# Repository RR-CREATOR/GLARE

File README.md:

# GLARE  
**Glasses Linked Augmented Reality Engine // By RR-CREATOR (rrop)**

---

## Table of Contents
- [GLARE](#glare)
  - [Intro](#intro)
  - [Why I made this](#why-i-made-this)
  - [PCB](#pcb)
    - [Power](#power)
    - [Main](#main)
    - [Full Board](#full-board)
  - [CAD](#cad)
    - [HUD](#hud)
    - [Camera](#camera)
    - [Frame](#frame)
    - [FULL CAD](#full-cad)
  - [BOM](#bom)

---

## GLARE

### Intro
GLARE is a Glasses Linked Augmented Reality Engine.  
It is basically a glasses attachment.  
It has a custom pcb, which you could place either inside the frame of glasses if you 3d print the frame, or attach it outside.  
It has a custom HUD made using birdbath optics and a 0.39" display, on one side, so you aren't too disconnected with reality, and a lot of the issues caused by cheap optics are resolved through seperate vision.  
It features an esp32-s3-wroom-n16r8 motherboard which, along with a phone(to be added after testing pcb), will get data from 2 mics, a camera, a gyro and gps and give an Augmented Reality experience through the HUD, for assitance in day to day life.

### Why I made this
I made this as I wanted to build something cheap and accessible, which could make AR glasses a reality for people.
I wanted it to be able to help people in need by translating written text it sees into users chosen language, and it can also
listen to conversations and show a live transcript in users chosen language, and can work for sign language as well.

---

## PCB
It has a custom pcb which serves as its mainboard.

### Power
The pcb has proper power management, and is powered by two batteries in parallel connected to a voltage supervisor.

The pcb also has a micro usb b port which is used to charge the LiPo batteries and is also used for programming the esp 32 module on the board.

It also has a battery gauge, and a power on/off button, along with a low power isolation.

It also has a 5V boost and a 5V to 3.3V LDO to power esp and other peripherals.

### Main
The pcb also has connections for various peripherals, including 2 mics for stereo sound, a camera, a micro oled display, a gps and gyro.

It also has a usb to uart module to programme this esp 32.

### Full Board

**Fully Traced Board:**  

**3D Model of PCB:**  

> Ik the pcb looks lik a cheap cybertruck :3

---

## CAD

### HUD
So the CAD has a representation of the HUD, attached to a small piece, to attach it to the frame.  
(the pieces of the hud will be glued with optically clear glue)

### Camera
It also has a small holder where the camera will go. The holder has an extended piece using which it will be glued to the glasses.

### Frame
The right leg/handle of the glasses frame has a simple design, with its bottom looking like a battery.

The left leg/handle on the other hand is modelled around the shape of the pcb, and is hollow with a cover so that the pcb can be enclosed in it.  
Also, it bottom is hollow, and designed so that a battery can be placed inside it.

### FULL CAD

---

## BOM

<table>
    <tr>
        <td>Category</td>
        <td>Component</td>
        <td>Part Number / Source</td>
        <td>Price (USD)</td>
        <td>Quantity</td>
        <td>Notes</td>
    </tr>
    <tr>
        <td>Core</td>
        <td>ESP32-S3-WROOM-1U-N16R8</td>
        <td>https://lcsc.com/product-detail/WiFi-Modules_ESPRESSIF-ESP32-S3-WROOM-1U-N16R8_C3013946.html?s_z=n_ESP32-S3-WROOM-1U-N16R8</td>
        <td>5.66</td>
        <td>1</td>
        <td>Core chip with wifi and bt</td>
    </tr>
    <tr>
        <td>Antenna</td>
        <td>Ezurio 001-0014</td>
        <td>https://www.digikey.com/en/products/detail/ezurio/001-0014/4732758</td>
        <td>3.41</td>
        <td>1</td>
        <td>2.4GHz for core</td>
    </tr>
    <tr>
        <td>Mosfet</td>
        <td>PMZ350UPEYL</td>
        <td>https://lcsc.com/product-detail/MOSFETs_Nexperia-PMZ350UPEYL_C478207.html?s_z=n_PMZ350UPEYL</td>
        <td>0.43</td>
        <td>10</td>
        <td>For display power switch</td>
    </tr>
    <tr>
        <td>USB to UART</td>
        <td>CH9102F</td>
        <td>https://lcsc.com/product-detail/USB-Converters_WCH-CH9102F_C2858418.html?s_z=n_CH9102F</td>
        <td>1.33</td>
        <td>1</td>
        <td>For Programming</td>
    </tr>
    <tr>
        <td>I�S Microphone</td>
        <td>SPH0645LM4H-B-8</td>
        <td>https://lcsc.com/product-detail/MEMS-Microphones_Knowles-SPH0645LM4H-B-8_C19190864.html?s_z=n_SPH0645LM4H-B</td>
        <td>8</td>
        <td>2</td>
        <td>MEMS microphone</td>
    </tr>
    <tr>
        <td>Transistors</td>
        <td>2SC4617R</td>
        <td>https://lcsc.com/product-detail/Bipolar-BJT_CBI-2SC4617R_C2836080.html?s_z=n_2SC4617R%2520BR</td>
        <td>0.35</td>
        <td>20</td>
        <td>Programming</td>
    </tr>
    <tr>
        <td>RGB LEDs</td>
        <td>WS2812B 2020</td>
        <td>https://lcsc.com/product-detail/RGB-LEDs-Built-in-IC_Worldsemi-WS2812B-2020_C965555.html?s_z=n_ws2812b%25202020</td>
        <td>0.41</td>
        <td>5</td>
        <td>For visual indication</td>
    </tr>
    <tr>
        <td>Micro USB B</td>
        <td>1050170001</td>
        <td>https://lcsc.com/product-detail/USB-Connectors_MOLEX-1050170001_C136000.html?s_z=n_C136000</td>
        <td>1.67</td>
        <td>1</td>
        <td>Charging LiPo</td>
    </tr>
    <tr>
        <td>Battery Charger</td>
        <td>AP5054HTCER</td>
        <td>https://lcsc.com/product-detail/Battery-Management_Wuxi-Chipown-Micro-electronics-AP5054HTCER_C2843820.html?s_z=n_ap5054htc</td>
        <td>0.15</td>
        <td>1</td>
        <td>Charging LiPo</td>
    </tr>
    <tr>
        <td>Low Voltage Detector</td>
        <td>XC61CC3002MR-G</td>
        <td>https://lcsc.com/product-detail/Supervisor-and-Reset-ICs_TOREX-XC61CC3002MR-G_C2456347.html?s_z=n_XC61CC3002MR</td>
        <td>0.92</td>
        <td>5</td>
        <td>Voltage Supervisor</td>
    </tr>
    <tr>
        <td>Battery Fuel Gauge</td>
        <td>MAX17048</td>
        <td>https://lcsc.com/product-detail/Battery-Management-ICs_Maxim-Integrated-MAX17048G-T10_C2682616.html</td>
        <td>4.16</td>
        <td>1</td>
        <td>Battery Percent</td>
    </tr>
    <tr>
        <td>Voltage Boost</td>
        <td>SY7088</td>
        <td>https://lcsc.com/product-detail/DC-DC-Converters_Silergy-SY7088DGC_C178240.html?s_z=n_SY7088</td>
        <td>1.52</td>
        <td>5</td>
        <td>Convert input to 5V</td>
    </tr>
    <tr>
        <td>LDO</td>
        <td>NCP167BMX330TBG</td>
        <td>https://lcsc.com/product-detail/Voltage-Regulators-Linear-Low-Drop-Out-LDO-Regulators_onsemi-NCP167BMX330TBG_C892227.html?s_z=n_NCP167BMX330TBG</td>
        <td>0.44</td>
        <td>1</td>
        <td>Convert 5V to 3.3V</td>
    </tr>
    <tr>
        <td>Schottky Diode</td>
        <td>RB160M-30</td>
        <td>https://lcsc.com/product-detail/Schottky-Diodes_High-Diode-RB160M-30_C2937163.html?s_z=n_C2937163</td>
        <td>0.38</td>
        <td>5</td>
        <td>Prevent back current in battery bypass</td>
    </tr>
    <tr>
        <td>Camera Module</td>
        <td>0V5640 160 AF</td>
        <td>https://www.aliexpress.com/item/3256806547258124.html?spm=a2g0o.productlist.main.7.3c04XpCAXpCAlF&amp;algo_pvid=1d8c60dc-197a-45e0-b911-5db3740a960b&amp;algo_exp_id=1d8c60dc-197a-45e0-b911-5db3740a960b-6&amp;pdp_ext_f=%7B%22order%22%3A%2248%22%2C%22eval%22%3A%221%22%7D&amp;pdp_npi=4%40dis%21USD%2125.14%216.32%21%21%21179.58%2145.16%21%40211b807017537824501694005e7310%2112000038123858641%21sea%21US%216130365553%21ABX&amp;curPageLogUid=NL6oj7jsGhIm&amp;utparam-url=scene%3Asearch%7Cquery_from%3A#nav-specification</td>
        <td>12.75</td>
        <td>1</td>
        <td>5MP autofocus camera</td>
    </tr>
    <tr>
        <td>Gyro + Accelo + Magneto</td>
        <td>ICM-20948</td>
        <td>https://lcsc.com/search?q=ICM-20948&amp;s_z=n_ICM-20948</td>
        <td>4.68</td>
        <td>1</td>
        <td>6-axis IMU</td>
    </tr>
    <tr>
        <td>GPS Module</td>
        <td>L86-M33</td>
        <td>https://www.mouser.in/ProductDetail/Quectel/L86-M33?qs=GedFDFLaBXFvEvNOo6IDYg%3D%3D</td>
        <td>12.82</td>
        <td>1</td>
        <td>Low-power GPS module</td>
    </tr>
    <tr>
        <td>Micro Oled Display</td>
        <td>ET039XGM OLED display + HDMI driver board</td>
        <td>Alibaba (including shipping) </td>
        <td>30</td>
        <td>1</td>
        <td>For HUD</td>
    </tr>
    <tr>
        <td>Mosfet main battery</td>
        <td>YJQD30P02A</td>
        <td>https://lcsc.com/product-detail/MOSFETs_YANGJIE-YJQD30P02A_C919546.html?s_z=n_C919546</td>
        <td>1.36</td>
        <td>5</td>
        <td>Mosfet for high power switching</td>
    </tr>
    <tr>
        <td>Mosfet main battery</td>
        <td>PMZ290UNE2YL</td>
        <td>https://lcsc.com/product-detail/MOSFETs_Nexperia-PMZ290UNE2YL_C478155.html?s_z=n_C478155</td>
        <td>0.53</td>
        <td>10</td>
        <td>Mosfet for high power switching</td>
    </tr>
    <tr>
        <td>Resistor</td>
        <td>10k ohm</td>
        <td>https://lcsc.com/product-detail/Chip-Resistor-Surface-Mount_FOJAN-FRC0402J103-TS_C2906885.html?s_z=n_C2906885</td>
        <td>0.05</td>
        <td>100</td>
        <td>Resistor</td>
    </tr>
    <tr>
        <td>Resistor</td>
        <td>150ohm</td>
        <td>https://lcsc.com/product-detail/Chip-Resistor-Surface-Mount_FOJAN-FRC0402F1500TS_C2909321.html?s_z=n_150ohm%2520resistor%25200402</td>
        <td>0.05</td>
        <td>100</td>
        <td>Resistor</td>
    </tr>
    <tr>
        <td>Resistor</td>
        <td>100k ohm</td>
        <td>https://lcsc.com/product-detail/Chip-Resistor-Surface-Mount_YAGEO-RC0402JR-07100KL_C106234.html?s_z=n_C106234</td>
        <td>0.06</td>
        <td>100</td>
        <td>Resistor</td>
    </tr>
    <tr>
        <td>Resistor</td>
        <td>2k ohm</td>
        <td>https://lcsc.com/product-detail/Chip-Resistor-Surface-Mount_YAGEO-RC0402FR-072KL_C60488.html?s_z=n_C60488</td>
        <td>0.06</td>
        <td>100</td>
        <td>Resistor</td>
    </tr>
    <tr>
        <td>Resistor</td>
        <td>1M ohm</td>
        <td>https://lcsc.com/product-detail/Chip-Resistor-Surface-Mount_YAGEO-RC0402FR-071ML_C138033.html</td>
        <td>0.07</td>
        <td>100</td>
        <td>Resistor</td>
    </tr>
    <tr>
        <td>Resistor</td>
        <td>470k</td>
        <td>https://lcsc.com/product-detail/Chip-Resistor-Surface-Mount_YAGEO-AC0402JR-07470KL_C227380.html</td>
        <td>0.05</td>
        <td>100</td>
        <td>Resistor</td>
    </tr>
    <tr>
        <td>Resistor/Resettable Fuse</td>
        <td>1A</td>
        <td>https://lcsc.com/product-detail/Resettable-Fuses_JDTfuse-ASMD0805-100_C135331.html?s_z=n_%2509%25206V%25201A%2520100A%25201.95A%25200805%2520Resettable%2520Fuses%2520ROHS</td>
        <td>0.44</td>
        <td>10</td>
        <td>Charging LiPo</td>
    </tr>
    <tr>
        <td>Resistor</td>
        <td>147k</td>
        <td>https://lcsc.com/product-detail/Chip-Resistor-Surface-Mount_YAGEO-AC0402FR-07147KL_C226785.html</td>
        <td>0.11</td>
        <td>100</td>
        <td>Resistor</td>
    </tr>
    <tr>
        <td>Switch</td>
        <td>SPST Tactile Switch</td>
        <td>https://lcsc.com/product-detail/Tactile-Switches_USAKRO-UK-B0249-SP25Y_C493280.html</td>
        <td>0.85</td>
        <td>5</td>
        <td>User button</td>
    </tr>
    <tr>
        <td>Switch</td>
        <td>Slide Switch</td>
        <td>https://lcsc.com/product-detail/Slide-Switches_Korean-Hroparts-Elec-K3-1270L-F1_C145858.html?s_z=n_C145858</td>
        <td>0.72</td>
        <td>5</td>
        <td>Power on/off</td>
    </tr>
    <tr>
        <td>LiPo battery</td>
        <td>500mAh, 3.7V</td>
        <td>https://robu.in/product/500mah-pcm-protected-micro-li-po-battery-2/</td>
        <td>6</td>
        <td>2</td>
        <td>For power</td>
    </tr>
    <tr>
        <td>Optical Clear Glue</td>
        <td>LOCA</td>
        <td>https://www.aliexpress.com/item/2255800983414695.html?spm=a2g0o.cart.0.0.346938dabCE0Hi&amp;mp=1&amp;pdp_npi=5%40dis%21USD%21USD%208.86%21USD%208.86%21%21USD%208.86%21%21%21%402101c80217498686257907146e4775%2110000015016065790%21ct%21US%212680287963%21%211%210&amp;_gl=1*mod294*_gcl_aw*R0NMLjE3NDkwODQ1MzguQ2p3S0NBanczZl9CQmhBUEVpd0FhQTNLNUM0SENPdklDSDhYTkZoaGZOOU1fTHVsX1VhVEhQRWtIbXNTWE1wWWE5cmJjR3RUQjYwa0dSb0N0YUVRQXZEX0J3RQ..*_gcl_dc*R0NMLjE3NDkwODQ1MzguQ2p3S0NBanczZl9CQmhBUEVpd0FhQTNLNUM0SENPdklDSDhYTkZoaGZOOU1fTHVsX1VhVEhQRWtIbXNTWE1wWWE5cmJjR3RUQjYwa0dSb0N0YUVRQXZEX0J3RQ..*_gcl_au*MTk0NDQ1MTk2My4xNzQ0MzUwNDU3*_ga*MjgwMjg2NzcwLjE3NDk4NDY2MDg.*_ga_VED1YSGNC7*czE3NDk4NjQxMTEkbzQkZzEkdDE3NDk4Njg2MjYkajMkbDAkaDA.</td>
        <td>9</td>
        <td>1</td>
        <td>For optics arrangement</td>
    </tr>
    <tr>
        <td>Beam Splitter Cube</td>
        <td>10x10x10mm (including shipping) </td>
        <td>https://www.getuscart.com/beam-splitter-cube-optical-glass-dichroic-prism-ratio-5050-spectrome-sicence-3</td>
        <td></td>
        <td>22</td>
        <td>For optics arrangement</td>
    </tr>
    <tr>
        <td>Combiner</td>
        <td>22x20mm(including shipping)</td>
        <td>https://www.aliexpress.us/item/3256807745776887.html?spm=a2g0o.productlist.main.1.1410OiSaOiSa4e&amp;algo_pvid=768d6793-6f7f-49d5-bb5c-2114676308ea&amp;algo_exp_id=768d6793-6f7f-49d5-bb5c-2114676308ea-0&amp;pdp_ext_f=%7B%22order%22%3A%22-1%22%2C%22eval%22%3A%221%22%7D&amp;pdp_npi=4%40dis%21USD%2113.16%2112.50%21%21%2194.46%2189.74%21%402103247017541326536096357ee333%2112000042919022060%21sea%21US%210%21ABX&amp;curPageLogUid=gzjOi8g92PHn&amp;utparam-url=scene%3Asearch%7Cquery_from%3A</td>
        <td>17</td>
        <td>1</td>
        <td>For optics arrangement</td>
    </tr>
    <tr>
        <td>Capacitor</td>
        <td>1uF</td>
        <td>https://lcsc.com/product-detail/Multilayer-Ceramic-Capacitors-MLCC-SMD-SMT_Samsung-Electro-Mechanics-CL05A105KP5NNNC_C14445.html?s_z=n_C14445</td>
        <td>0.17</td>
        <td>100</td>
        <td>Capacitor</td>
    </tr>
    <tr>
        <td>Capacitor</td>
        <td>100nF</td>
        <td>https://lcsc.com/product-detail/Multilayer-Ceramic-Capacitors-MLCC-SMD-SMT_FH-0402B104K160NT_C41851.html?s_z=n_C41851</td>
        <td>0.1</td>
        <td>100</td>
        <td>Capacitor</td>
    </tr>
    <tr>
        <td>Capacitor</td>
        <td>200pF</td>
        <td>https://lcsc.com/product-detail/Multilayer-Ceramic-Capacitors-MLCC-SMD-SMT_YAGEO-CC0402KRX7R9BB201_C277481.html</td>
        <td>0.12</td>
        <td>100</td>
        <td>Capacitor</td>
    </tr>
    <tr>
        <td>Capacitor</td>
        <td>10uF</td>
        <td>https://lcsc.com/product-detail/Multilayer-Ceramic-Capacitors-MLCC-SMD-SMT_Samsung-Electro-Mechanics-CL05A106MQ5NUNC_C15525.html?s_z=n_C15525</td>
        <td>0.06</td>
        <td>10</td>
        <td>Capacitor</td>
    </tr>
    <tr>
        <td>Capacitor</td>
        <td>22uF</td>
        <td>https://lcsc.com/product-detail/Multilayer-Ceramic-Capacitors-MLCC-SMD-SMT_Murata-Electronics-GRM155R60J226ME11D_C415703.html</td>
        <td>0.73</td>
        <td>20</td>
        <td>Capacitor</td>
    </tr>
    <tr>
        <td>LED</td>
        <td>Red</td>
        <td>https://lcsc.com/product-detail/LED-Indication-Discrete_EVERLIGHT-16-213SURC-S530-A3-TR8_C136765.html?s_z=n_red%2520led%25200402</td>
        <td>0.31</td>
        <td>10</td>
        <td>For charging indication</td>
    </tr>
    <tr>
        <td>Inductor</td>
        <td>1.5uH</td>
        <td>https://lcsc.com/product-detail/power-inductors_prod-tech-pspmaa0402-1r5m-anp_C436514.html</td>
        <td>0.74</td>
        <td>5</td>
        <td>Inductor</td>
    </tr>
    <tr>
        <td>PCB</td>
        <td>PCBA</td>
        <td>JLC Estimate</td>
        <td>40</td>
        <td></td>
        <td></td>
    </tr>
    <tr>
        <td>LiPo battery voltage meter</td>
        <td>QP38</td>
        <td>https://www.amazon.in/Robodo-QP38-Battery-Voltage-Display/dp/B073Q2ZFKF/ref=sr_1_5?dib=eyJ2IjoiMSJ9.h7pNd3b94wMLvu7R9kZE2eSJ32hl1lhnJQFlfLN4Gd24xE82YwzUwkh3EBS-Zxmqhcc0an2tpR5LRth_B-KnNtE7pN8W4rJ_TZe33bOvyPOtQjmV_vAnpvKywwoU83I3_Bc8Cko2RWheYirfow74KHyUnrcHWWN3DNDxkwo70TQ92bP6v6UaLfMuhW-eBRelz3vvOtdu5FCXq483-jLx-jFEvNaK3QgiHRXgbmL0ei_d_NMcqqMmNXpsakkOPs9weZzdt04Jq2dVCNuaqMc5vZBn6DVezrGdwmTXT11ZPMo.22KFM2wXUmmHYRZHEpZpVcRkNnztCnI54vMCHYcmwyU&dib_tag=se&keywords=lipo+battery+voltage+meter&qid=1754327846&sr=8-5</td>
        <td>2.68</td>
        <td>1</td>
        <td>for testing lipo voltage</td>
    </tr>
    <tr>
        <td>LiPo battery charger</td>
        <td>Type C</td>
        <td>https://www.amazon.in/Converter-Overcharge-Over-Current-Protection-Module/dp/B0DNCRTZXD</td>
        <td>1.6</td>
        <td>1</td>
        <td>for charging lipo</td>
    </tr>
    <tr>
        <td>1.5m Cable</td>
        <td>USB C to Micro HDMI</td>
        <td>https://www.flipkart.com/microware-hdmi-cable-1-5-m-usb-3-1-type-c/p/itm928cffbd6b34a?pid=ACCF8DCB4FU6Z7SN&amp;lid=LSTACCF8DCB4FU6Z7SNBEGLNV&amp;marketplace=FLIPKART&amp;cmpid=content_data-cable_8965229628_gmc&amp;gPromoCode=Freedom_Sale_2025_All</td>
        <td>9</td>
        <td>1</td>
        <td>For display to work, without this display wont work</td>
    </tr>
    <tr>
        <td></td>
        <td></td>
        <td></td>
        <td></td>
        <td></td>
        <td></td>
    </tr>
    <tr>
        <td></td>
        <td></td>
        <td></td>
        <td></td>
        <td></td>
        <td></td>
    </tr>
    <tr>
        <td></td>
        <td></td>
        <td></td>
        <td></td>
        <td></td>
        <td></td>
    </tr>
</table>

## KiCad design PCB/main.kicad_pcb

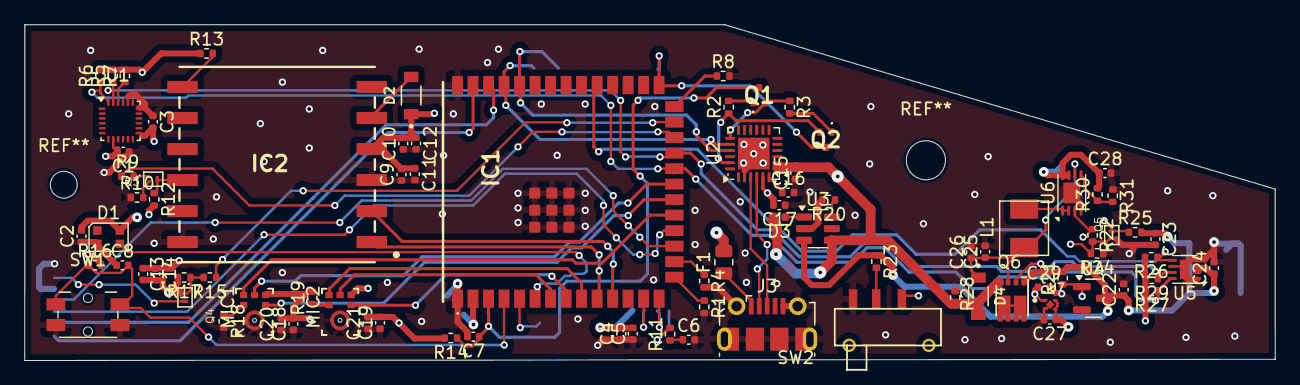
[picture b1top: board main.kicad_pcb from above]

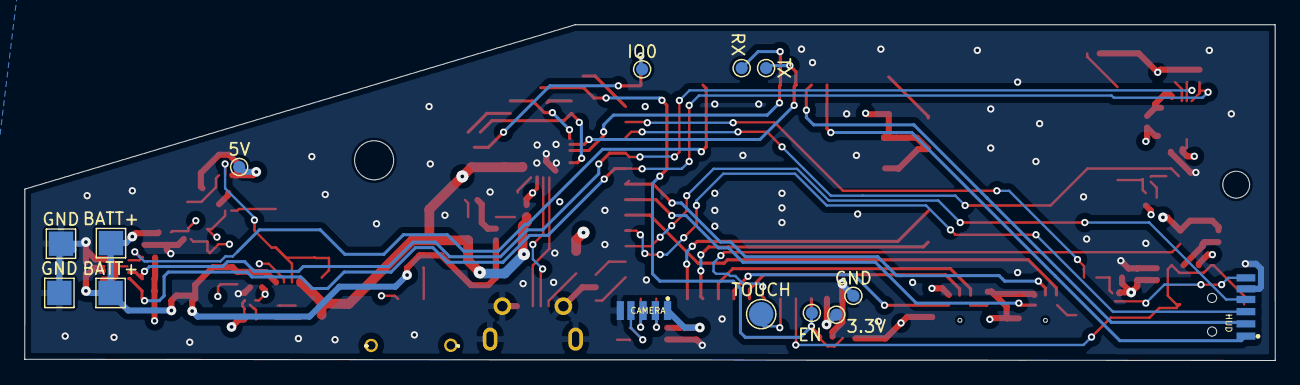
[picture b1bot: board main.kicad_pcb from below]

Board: 4 copper layers, 102.4 x 27.5 mm, 100 parts (14 on the bottom side), 64 nets.

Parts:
3.3V: 3V3; TestPoint_Pad_D1.0mm
5V: 5V; TestPoint_Pad_D1.0mm
BATT+: BATT1+; TestPoint_Pad_2.0x2.0mm
BATT+#2: BATT2+; TestPoint_Pad_2.0x2.0mm
C1, C3, C4, C6, C8, C9, C10, C14, C16, C17, C20, C21, C22, C24, C27: 100nF; C_0402_1005Metric
C2, C5, C7, C11, C12, C13, C15, C25, C29: 1uF; C_0402_1005Metric
C18, C19: 200pF; C_0402_1005Metric
C23, C26, C28: 22uF; C_0402_1005Metric
CAMERA: Camera; Solder-5P-Connector
D1: WS2812B-2020; LED_WS2812B-2020_PLCC4_2.0x2.0mm
D2, D4: RB160M-30; DIO_RB160M-30
D3: Red; D_0402_1005Metric
EN: EN; TestPoint_Pad_D1.0mm
F1: 1A; R_0805_2012Metric
GND: BATT1-; TestPoint_Pad_2.0x2.0mm
GND#2: GND; TestPoint_Pad_D1.0mm
GND#3: BATT2-; TestPoint_Pad_2.0x2.0mm
HUD: HUD; Solder-6P-Connector
IC1: ESP32-S3-WROOM-1U-N16R8; ESP32S3WROOM1UN16R8
IC2: L86-M33; L80-M39
IO0: IO0; TestPoint_Pad_D1.0mm
J3: USB_B_Micro; USB_Micro-B_Molex-105017-0001
L1: 1.5uH; 1.5uH_YXMAA0402-1R5M-ANP
MIC1, MIC2: SPH0645LM4H-B; SPH0645LM4H-B-2
Q1, Q2: 2SC4617-R-TP; 2SC4617RTP
Q3, Q4: PMZ350UPEYL; DFN100X60X40-3N
Q5: PMZ290UNE2YL; DFN100X60X40-3N
Q6: YJQD30P02A; EMF20B02V
R1, R2, R3, R4, R7, R8, R12, R13, R14, R15, R16, R18, R19, R23, R26: 10k; R_0402_1005Metric
R5, R6, R27, R29: 4.7k; R_0402_1005Metric
R9, R10: 1k; R_0402_1005Metric
R11, R25, R28: 1M; R_0402_1005Metric
R17, R21, R24: 100k; R_0402_1005Metric
R20: 2.1k; R_0402_1005Metric
R22: 150; R_0402_1005Metric
R30: 470k; R_0402_1005Metric
R31: 147k; R_0402_1005Metric
RX: RX; TestPoint_Pad_D1.0mm
SW1: SW_SPST; SMD_Switch_Panasonic_EVQPUL_EVQPUC_6.3x6.7
SW2: Power; SW_SMD_SPDT_Slide_9x6.9-hole
TOUCH: Touch Pad; TestPoint_Pad_D2.0mm
TX: TX; TestPoint_Pad_D1.0mm
U1: ICM-20948; InvenSense_QFN-24_3x3mm_P0.4mm
U2: CH9102F; QFN-24-1EP_4x4mm_P0.5mm_EP2.6x2.6mm
U3: AP5054HTC; SOT-23-6
U4: XC61CC3002MR; SOT-23
U5: MAX17048; DFN-8-1EP_2x2mm_P0.5mm_EP0.8x1.6mm
U6: SY7088; DFN-8-1EP_3x2mm_P0.5mm_EP1.7x1.4mm
U7: NCP167BMX330TBG; VREG_NCP167BMX330TBG

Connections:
+3.3V: 3.3V.1, C1.2, C3.2, C9.2, C10.2, C11.1, C12.1, C17.2, C18.2, C19.2, C20.2, C21.2, C29.1, D2.C, IC1.2 (3V3), IC2.4 (VCC), MIC1.5 (VDD), MIC2.5 (VDD), R5.2, R6.2, R7.2, R12.2, R13.1, R14.2, R16.2, R19.2, R26.2, R27.2, R29.2, U1.8 (VDDIO), U1.13 (VDD), U2.5 (VIO), U7.1 (OUT)
+5V: 5V.1, C2.2, C4.2, C5.2, C13.2, C14.2, C27.1, C28.1, CAMERA.1, D1.4 (VDD), Q4.2 (S), R17.2, R30.2, U6.7 (OUT), U6.8 (OUT), U7.3 (EN), U7.4 (IN)
ALRT: IC1.31 (IO38), R26.1, U5.5 (ALRT)
BATT+: BATT+.1, BATT+#2.1, C22.1, C23.1, C24.1, Q6.1 (S2), R21.2, R23.1, R25.2, U3.3 (BAT), U4.3 (VIN), U5.2 (CELL), U5.3 (Vdd)
BRT+: HUD.4, IC1.17 (IO9)
BRT-: HUD.3, IC1.18 (IO10)
D+: CAMERA.3, IC1.14 (IO20)
D-: CAMERA.2, IC1.13 (IO19)
DTR: Q2.2 (E), R2.1, U2.23 (~DTR)
EN: C7.1, EN.1, IC1.3 (EN), Q1.3 (C), R14.1
GND: C1.1, C2.1, C3.1, C4.1, C5.1, C6.2, C7.2, C8.1, C9.1, C10.1, C11.2, C12.2, C13.1, C14.1, C15.1, C16.2, C17.1, C18.1, C19.1, C20.1, C21.1, C22.2, C23.2, C24.2, C25.2, C26.2, C27.2, C28.2, C29.2, CAMERA.5, D1.2 (VSS), GND.1, GND#2.1, GND#3.1, HUD.5, IC1.1 (GND_1), IC1.40 (GND_2), IC1.41 (GND_3), IC1.42 (GND_4), IC1.43 (GND_5), IC1.44 (GND_6), IC1.45 (GND_7), IC1.46 (GND_8), IC1.47 (GND_9), IC1.48 (GND_10), IC1.49 (GND_11), IC2.3 (GND_1), IC2.12 (GND_2), J3.5 (GND), J3.6 (Shield), MIC1.3 (GND), MIC2.3 (GND), Q5.2 (S), R1.2, R4.2, R8.2, R10.1, R18.2, R20.2, R24.1, R28.1, R31.1, SW1.2 (B), SW2.1 (A), U1.18 (GND), U1.20 (GND), U2.2 (GND), U2.25 (GND), U3.2 (GND), U4.2 (GND/VSS), U5.1 (CTG), U5.4 (GND), U5.6 (QSTRT), U5.9 (EP), U6.4 (GND), U6.9 (Pad), U7.2 (GND), U7.5 (EPAD)
GRX: IC1.10 (IO17), IC2.1 (RXD1)
GTX: IC1.11 (IO18), IC2.2 (TXD1)
HUD+: HUD.6, Q4.3 (D)
HUD_EN: IC1.25 (IO48), R15.1
I2SCLK1: IC1.20 (IO12), MIC1.4 (BCLK)
I2SCLK2: IC1.8 (IO15), MIC2.4 (BCLK)
I2SDATA1: IC1.21 (IO13), MIC1.6 (DATA_OUT)
I2SDATA2: IC1.7 (IO7), MIC2.6 (DATA_OUT)
I2SWS1: IC1.19 (IO11), MIC1.1 (WS)
I2SWS2: IC1.9 (IO16), MIC2.1 (WS)
IO0: IC1.27 (IO0), IO0.1, Q2.3 (C)
unnamed: C6.1, R11.1
unnamed: D3.1 (K), U3.1 (~CHRG)
unnamed: IC1.15 (IO3), R1.1
unnamed: IC1.26 (IO45), R8.1
unnamed: IC1.16 (IO46), R4.1
unnamed: IC2.7 (FORCE_ON), R13.2
unnamed: IC2.10 (RESET), Q3.3 (D), R12.1
unnamed: D2.A, IC2.5 (V_BCKP)
unnamed: CAMERA.4, R11.2
unnamed: F1.1, J3.1 (VBUS)
unnamed: L1.2, U6.1 (LX), U6.2 (LX)
unnamed: MIC1.2 (SELECT), R18.1
unnamed: MIC2.2 (SELECT), R19.1
unnamed: Q1.1 (B), R2.2
unnamed: Q2.1 (B), R3.2
unnamed: Q3.1 (G), R9.2
unnamed: Q3.2 (S), R10.2
unnamed: Q4.1 (G), R15.2, R17.1
unnamed: Q5.3 (D), Q6.2 (G2), R25.1
unnamed: Q5.1 (G), R22.2, R24.2, SW2.2 (B)
unnamed: Q6.5 (D2), Q6.6 (D2), Q6.7 (D2), Q6.8 (D2)
unnamed: C25.1, C26.1, D4.C, L1.1, Q6.3 (S2), U6.6 (IN)
unnamed: R23.2, SW2.3 (C)
unnamed: R7.1, U1.22 (~CS)
unnamed: C16.1, U2.6 (V3)
unnamed: R20.1, U3.6 (PROG)
unnamed: R30.1, R31.2, U6.5 (FB)
PSEN: R21.1, R22.1, U4.1 (VOUT), U6.3 (EN)
RESETGPS: IC1.24 (IO47), R9.1
RGB: D1.3 (DIN), IC1.6 (IO6)
RTS: Q1.2 (E), R3.1, U2.19 (~RTS)
RX_ESP: IC1.36 (RXD0), RX.1, U2.21 (TXD)
RX_esp_hud: HUD.2, IC1.38 (IO2)
SCL: IC1.23 (IO21), R5.1, R29.1, U1.23 (SCL/SCLK), U5.7 (SCL)
SDA: IC1.22 (IO14), R6.1, R27.1, U1.24 (SDA/SDI), U5.8 (SDA)
Switch: C8.2, IC1.4 (IO4), R16.1, SW1.1 (A)
TX_ESP: IC1.37 (TXD0), TX.1, U2.20 (RXD)
TX_esp_hud: HUD.1, IC1.39 (IO1)
Touch: IC1.5 (IO5), TOUCH.1
USB+: J3.3 (D+), U2.3 (UD+)
USB-: J3.2 (D-), U2.4 (UD-)
VBUS: C15.2, D3.2 (A), D4.A, F1.2, Q6.4 (G2), R28.2, U2.7 (VDD5), U2.8 (VBUS), U3.4 (VCC)

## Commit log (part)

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2025-08-02 Rename Frame with electronics and hud v2.step to CAD/Frame with electronics and hud v2.step
2026-06-29 Complete ESP32-S3 firmware with live transcription
    Fix I2S mic init (wrong clock, wrong slot width for SPH0645, never enabled)
    Add microphones_read() for actual PCM capture
    Add WiFi + WebSocket streaming pipeline (glare_net.c)
    Add HUD text output (hud_show/hud_show_n over UART)
    Wire app_main with NVS init and full boot sequence
    Add glare_config.h for WiFi/WS/audio config
